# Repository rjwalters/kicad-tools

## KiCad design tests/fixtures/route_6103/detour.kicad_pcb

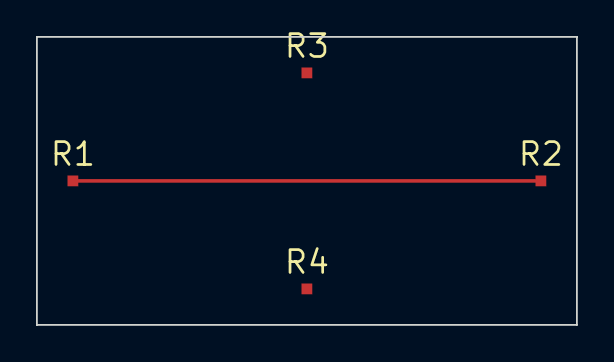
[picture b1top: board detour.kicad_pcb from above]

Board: 2 copper layers, 30.0 x 16.0 mm, 4 parts (0 on the bottom side), 2 nets.

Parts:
R1, R2, R3, R4: 10k; R_0603_1608Metric

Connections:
/A: R1.1, R2.1
/B: R3.1, R4.1

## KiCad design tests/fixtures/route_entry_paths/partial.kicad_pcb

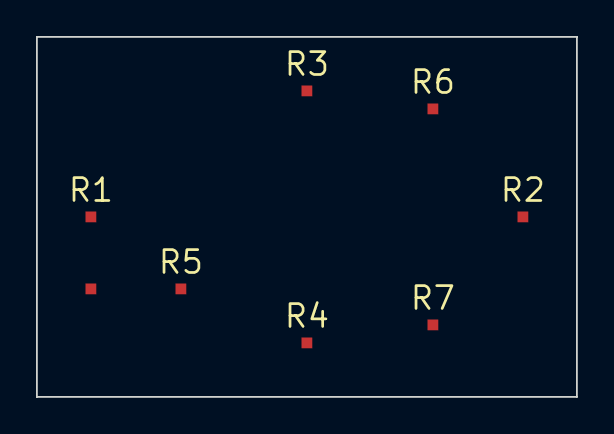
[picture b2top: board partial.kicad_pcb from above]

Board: 2 copper layers, 30.0 x 20.0 mm, 7 parts (0 on the bottom side), 4 nets, no tracks yet.

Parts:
R1, R2, R3, R4, R5, R6, R7: 10k; R_0603_1608Metric

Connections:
/A: R1.1, R2.1
/B: R3.1, R4.1
/C: R1.2, R5.1
/D: R6.1, R7.1
